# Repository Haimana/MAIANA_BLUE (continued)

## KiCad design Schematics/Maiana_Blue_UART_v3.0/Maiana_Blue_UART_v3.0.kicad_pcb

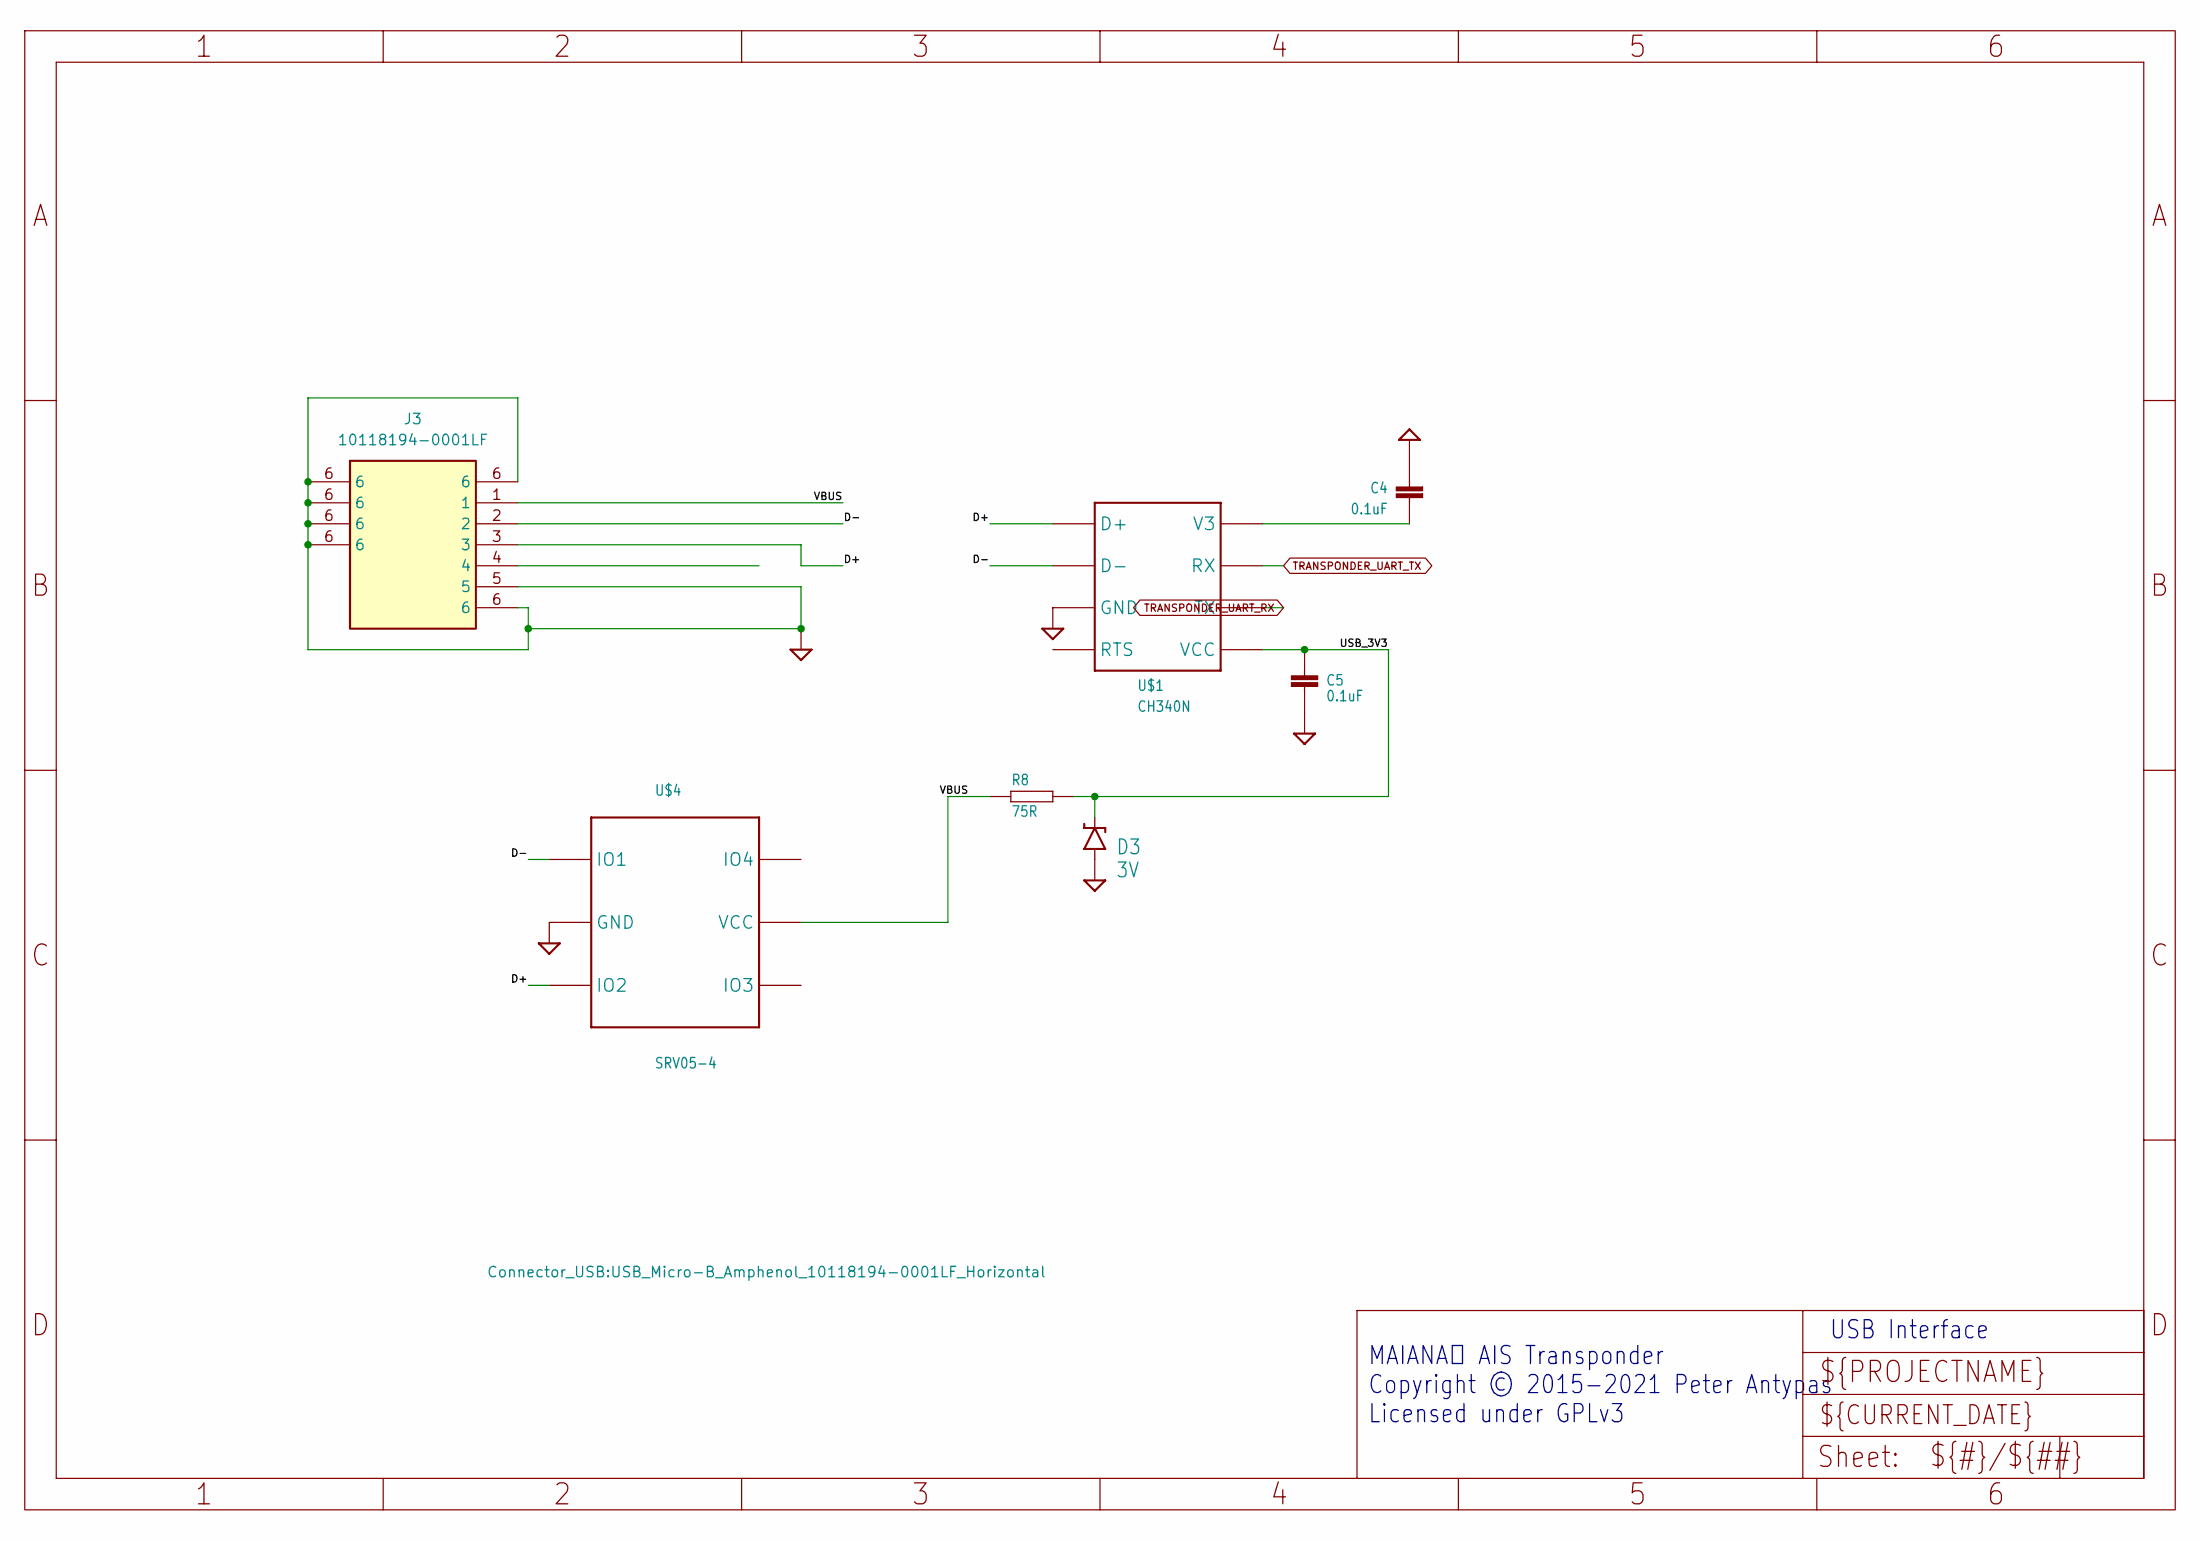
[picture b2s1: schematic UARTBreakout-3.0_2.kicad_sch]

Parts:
C4, C5: 0.1uF; 0603
D3: 3V; SOD-323
J3: 10118194-0001LF; USB_Micro-B_Amphenol_10118194-0001LF_Horizontal; Manufacturer_Part_Number 10118194-0001LF
R8: 75R; 0603
U$1: CH340N; SOIC-8; PARTNO CH340N
U$4: SRV05-4; SOT23-6

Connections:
/UARTBreakout-3.0_2/D+: J3.3, U$1.1 (D+), U$4.3 (IO2)
/UARTBreakout-3.0_2/D-: J3.2, U$1.2 (D-), U$4.1 (IO1)
/UARTBreakout-3.0_2/USB_3V3: C5.P$1 (1), D3.C, R8.P$2, U$1.5 (VCC)
/UARTBreakout-3.0_2/VBUS: J3.1, R8.P$1, U$4.5 (VCC)
GND: C4.P$2 (2), C5.P$2 (2), D3.A, J3.5, J3.6, U$1.3 (GND), U$4.2 (GND); also elsewhere on the board
unnamed: C4.P$1 (1), U$1.8 (V3)
TRANSPONDER_UART_RX: U$1.6 (TX); also elsewhere on the board
TRANSPONDER_UART_TX: U$1.7 (RX); also elsewhere on the board

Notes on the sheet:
USB Interface
MAIANA™ AIS Transponder Copyright © 2015-2021 Peter Antypas Licensed under GPLv3

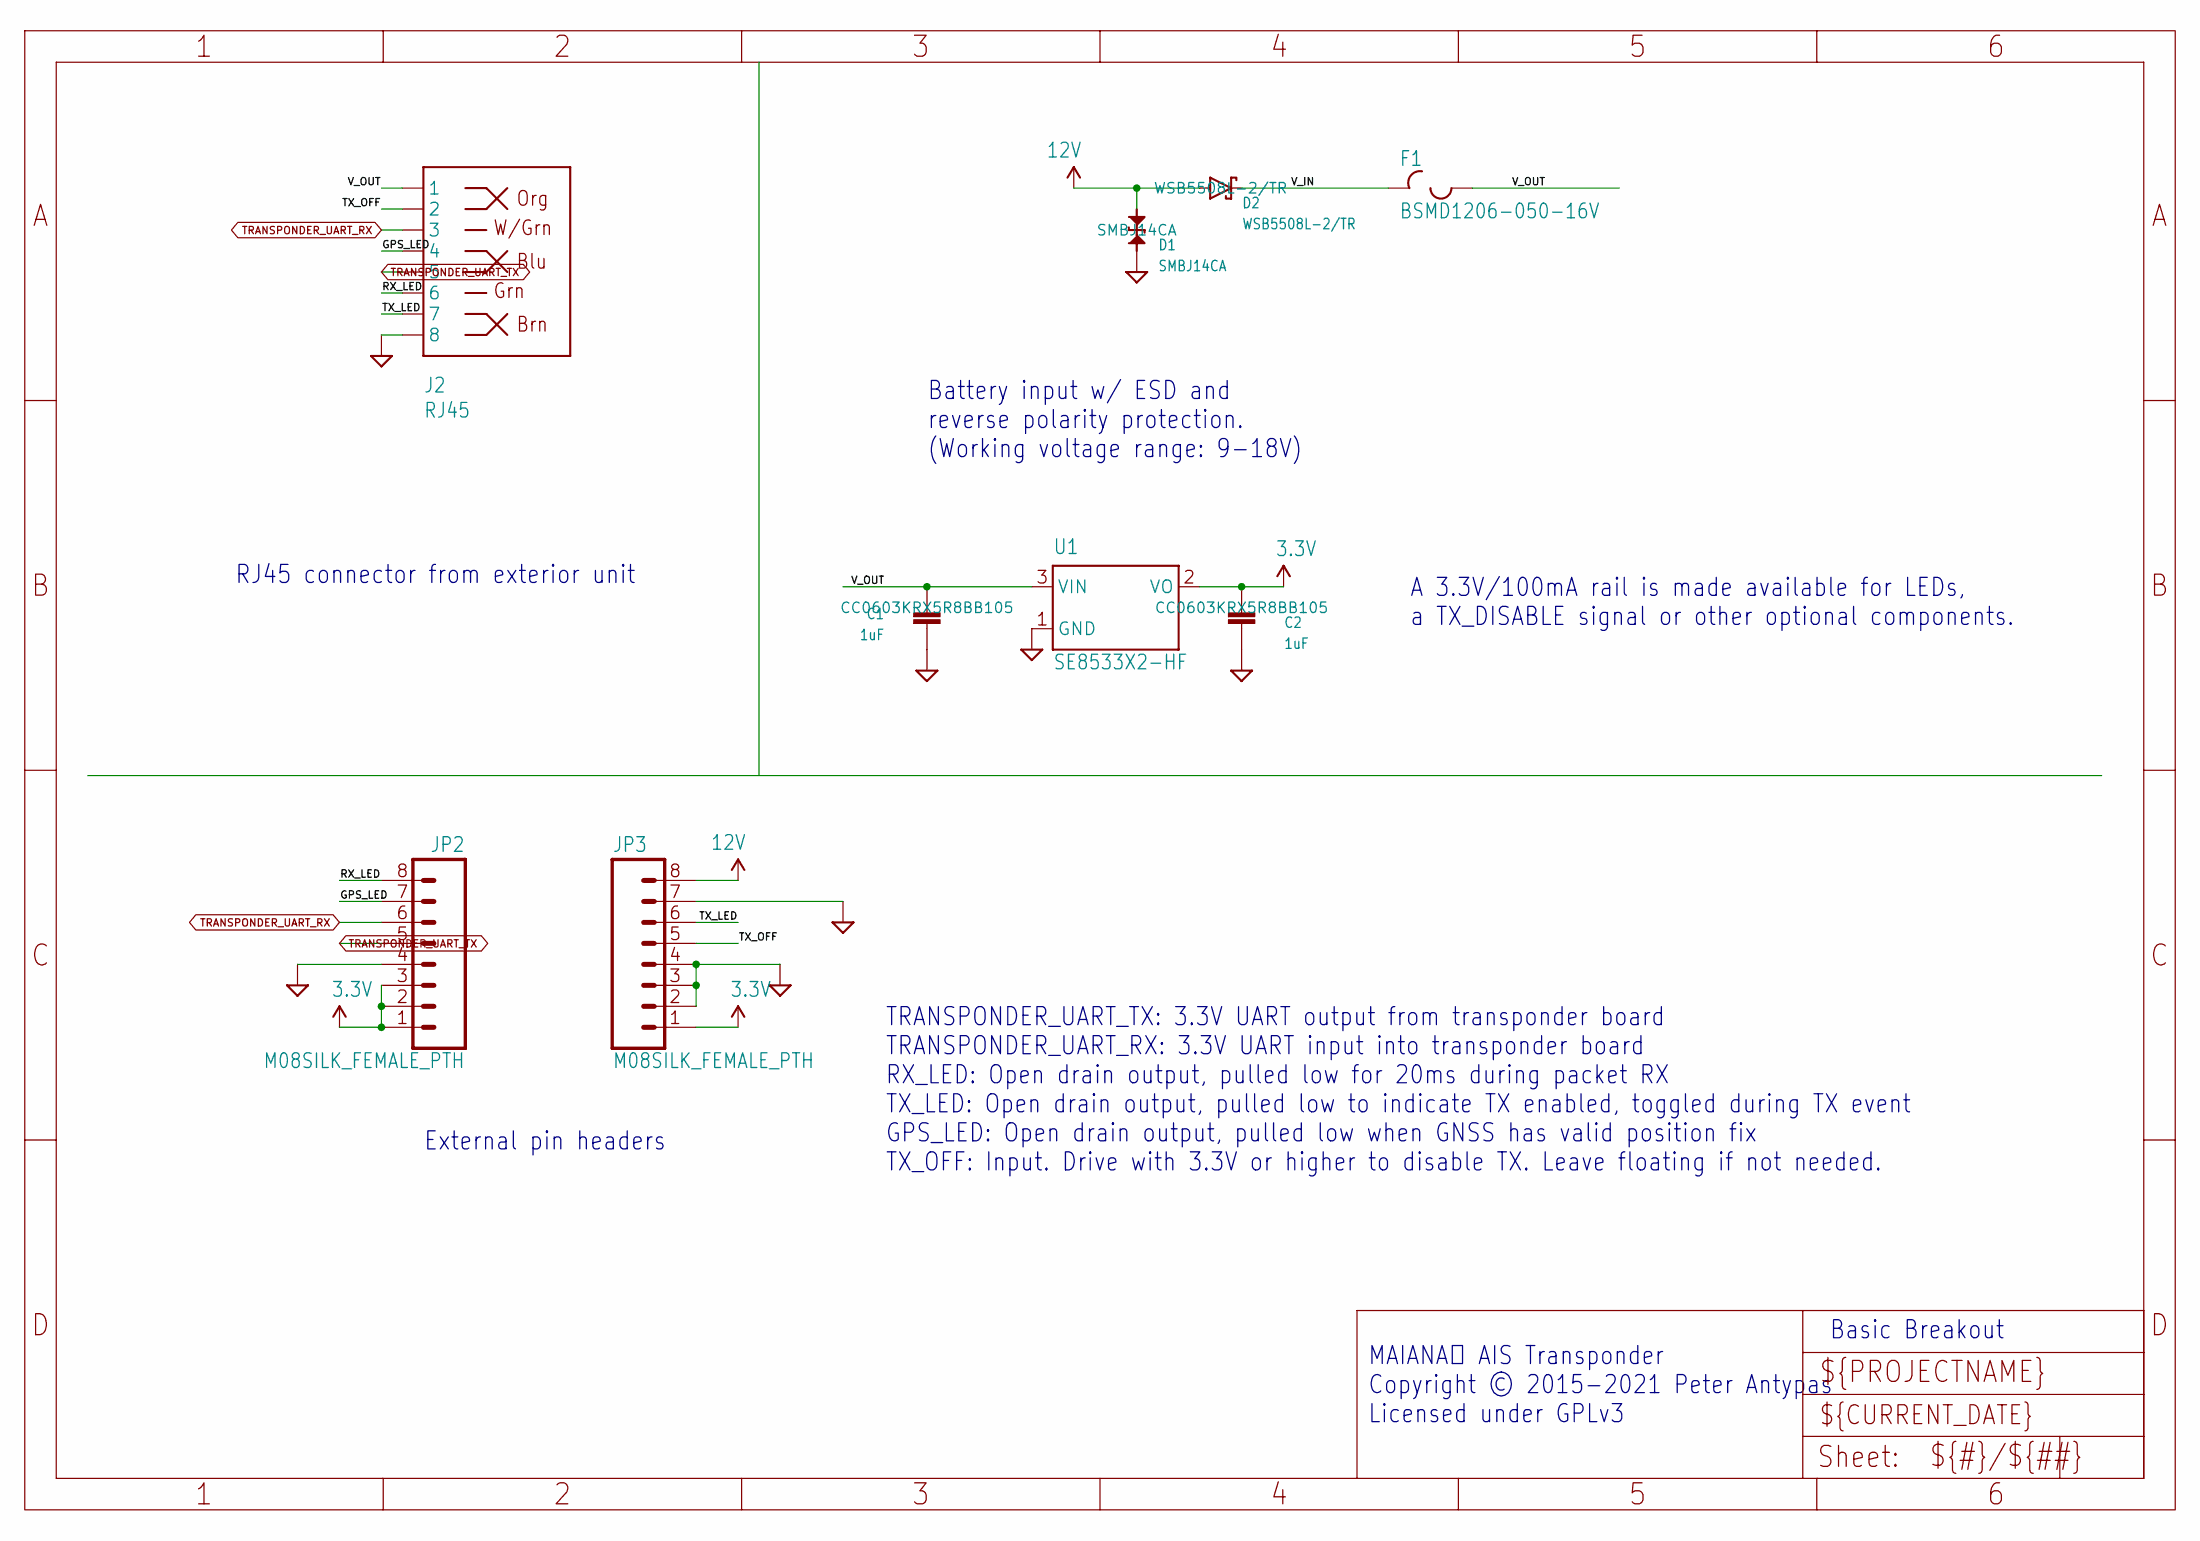
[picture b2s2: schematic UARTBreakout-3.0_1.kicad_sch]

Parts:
C1, C2: 1uF; 0603; PARTNO CC0603KRX5R8BB105
D1: SMBJ14CA; SMB-BIDIR; PARTNO SMBJ14CA
D2: WSB5508L-2/TR; SOD123; PARTNO WSB5508L-2/TR
F1: BSMD1206-050-16V; R1206; PARTNO BSMD1206-050-16V
J2: RJ45; RJ45-8; PARTNO 95501-2821
JP2, JP3: M08SILK_FEMALE_PTH; 1X08
U1: SE8533X2-HF; SOT23; PARTNO SE8533X2-HF

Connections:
3.3V: C2.P$1 (1), JP2.1, JP2.2, JP2.3, JP3.1, U1.2 (VO)
12V: D1.A, D2.A, JP3.8
/UARTBreakout-3.0_1/GPS_LED: J2.4, JP2.7
/UARTBreakout-3.0_1/RX_LED: J2.6, JP2.8
/UARTBreakout-3.0_1/TX_LED: J2.7, JP3.6
/UARTBreakout-3.0_1/TX_OFF: J2.2, JP3.5
/UARTBreakout-3.0_1/V_IN: D2.C, F1.1
/UARTBreakout-3.0_1/V_OUT: C1.P$1 (1), F1.2, J2.1, U1.3 (VIN)
GND: C1.P$2 (2), C2.P$2 (2), D1.C, J2.8, JP2.4, JP3.2, JP3.3, JP3.4, JP3.7, U1.1 (GND); also elsewhere on the board
TRANSPONDER_UART_RX: J2.3, JP2.6; also elsewhere on the board
TRANSPONDER_UART_TX: J2.5, JP2.5; also elsewhere on the board

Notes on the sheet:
TRANSPONDER_UART_TX: 3.3V UART output from transponder board TRANSPONDER_UART_RX: 3.3V UART input into transponder board RX_LED: Open drain output, pulled low for 20ms during packet RX TX_LED: Open drain output, pulled low to indicate TX enabled, toggled during TX event GPS_LED: Open drain output, 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
RJ45 connector from exterior unit
Basic Breakout
Battery input w/ ESD and reverse polarity protection. (Working voltage range: 9-18V)
A 3.3V/100mA rail is made available for LEDs, a TX_DISABLE signal or other optional components.
External pin headers
MAIANA™ AIS Transponder Copyright © 2015-2021 Peter Antypas Licensed under GPLv3

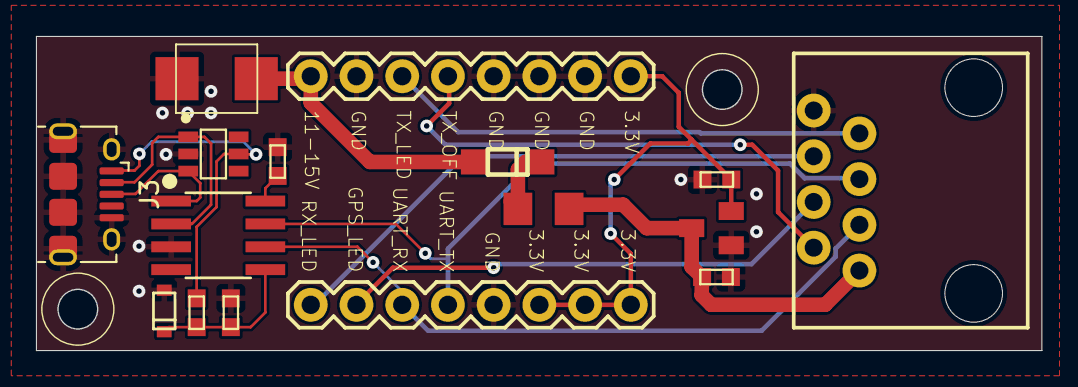
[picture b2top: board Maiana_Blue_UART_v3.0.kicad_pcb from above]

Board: 2 copper layers, 55.9 x 17.5 mm, 16 parts (0 on the bottom side), 16 nets.

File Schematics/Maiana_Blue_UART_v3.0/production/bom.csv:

Designator,Footprint,Quantity,Value,LCSC Part #
"C1, C2",0603,2,1uF,
"C4, C5",0603,2,0.1uF,
D1,SMB-BIDIR,1,SMBJ14CA,
D2,SOD123,1,WSB5508L-2/TR,
D3,SOD-323,1,3V,
F1,R1206,1,BSMD1206-050-16V,
J3,USB_Micro-B_Amphenol_10118194-0001LF_Horizontal,1,10118194-0001LF,
R8,0603,1,75R,
U$1,SOIC-8,1,CH340N,
U1,SOT23,1,SE8533X2-HF,

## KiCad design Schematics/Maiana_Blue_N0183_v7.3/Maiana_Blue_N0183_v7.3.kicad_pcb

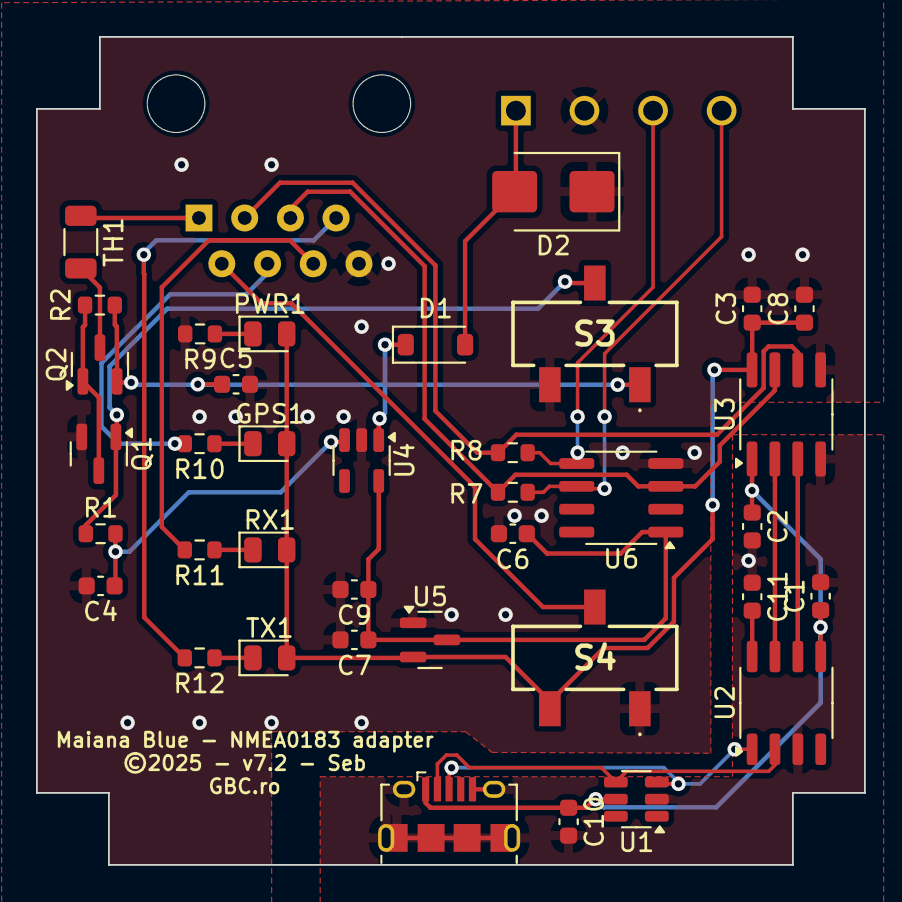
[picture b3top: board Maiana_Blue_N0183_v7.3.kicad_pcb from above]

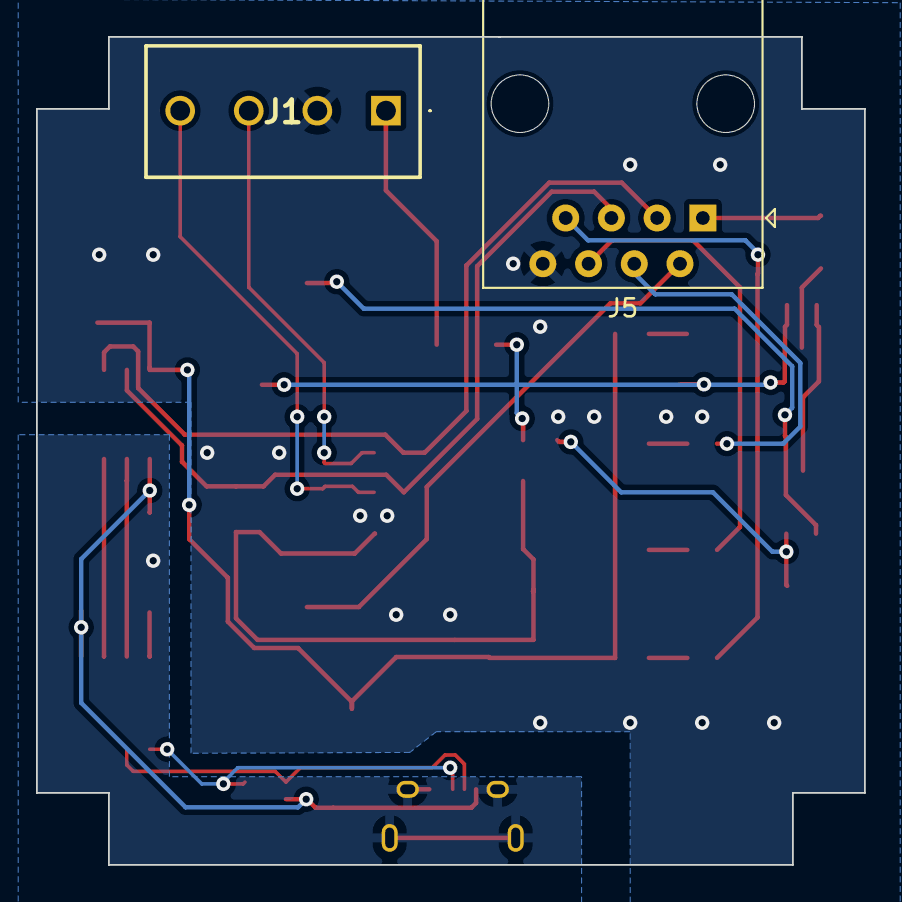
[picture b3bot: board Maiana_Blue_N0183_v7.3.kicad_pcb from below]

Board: 2 copper layers, 46.0 x 46.0 mm, 39 parts (2 on the bottom side), 29 nets.

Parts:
C1, C2, C3, C9, C10, C11: 0.1uF; C_0603_1608Metric
C4, C5, C6, C7, C8: 1uF; C_0603_1608Metric
D1: WSB5508L-2/TR; D_SOD-123
D2: SMBJ16CA; D_SMB
GPS1: KT-0805G; LED_0805_2012Metric
J1: 1727036
J3: USB_B_Micro; USB_Micro-B_Amphenol_10118194_Horizontal
J5: 54602-908LF; RJ45_Amphenol_54602-x08_Horizontal
PWR1: KT-0805G; LED_0805_2012Metric
Q1: BSS138; SOT-23
Q2: AO3401A; SOT-23
R1, R2: 10k; R_0603_1608Metric
R7, R8: 0R; R_0603_1608Metric
R9, R10, R11, R12: 2k2; R_0603_1608Metric
RX1: KT-0805G; LED_0805_2012Metric
S3, S4: MS-12D17-G2; MS12D17G2
TH1: Thermistor_PTC; R_1206_3216Metric
TX1: KT-0805G; LED_0805_2012Metric
U1: SRV05-4; SOT-23-6
U2: CH340N; SO-8_3.9x4.9mm_P1.27mm
U3: ADuM121N; SOIC-8_3.9x4.9mm_P1.27mm
U4: TJ5205SF5-5.0; SOT-23-5
U5: SE8533X2-HF; SOT-23
U6: DS8921M; SOIC-8_3.9x4.9mm_P1.27mm

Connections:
+3.3V: C3.1, C8.1, GPS1.2 (A), PWR1.2 (A), RX1.2 (A), S4.2, TX1.2 (A), U3.8 (VDD2), U5.2 (VO)
+5V: C6.1, C7.1, C9.1, U4.5 (VOUT), U5.3 (VI), U6.1 (VCC)
+12V: D1.2 (A), D2.2, J1.1
/TX_DISABLE: J5.2, S4.3
/VBUS: C1.1, C2.1, C10.1, J3.1 (VBUS), U1.5 (VP), U2.5 (VCC), U3.1 (VDD1)
/V_IN: C5.1, D1.1 (K), Q2.2 (S), R2.2, S3.1, U4.1 (VIN)
AIS_RX_EVENT: J5.6, R11.2
AIS_TX_EVENT: J5.7, R12.2
D+: J3.3 (D+), U1.3 (IO2), U2.1 (D+)
D-: J3.2 (D-), U1.4 (IO3), U2.2 (D-)
GND: C3.2, C4.2, C5.2, C6.2, C7.2, C8.2, C9.2, D2.1, J1.2, J5.8, Q1.2 (S), R9.2, S3.2, S4.1, U3.5 (GND2), U4.2 (GND), U5.1 (GND), U6.4 (GND)
GND2: C1.2, C2.2, C10.2, C11.1, J3.5 (GND), J3.6 (Shield), U1.2 (VN), U2.3 (GND), U3.4 (GND1)
GPS_STATUS: J5.4, R10.2
NMEA+: J1.4, R7.1, U6.6 (DO)
NMEA-: J1.3, R8.1, U6.5 (~DO)
unnamed: GPS1.1 (K), R10.1
unnamed: PWR1.1 (K), R9.1
unnamed: Q1.3 (D), Q2.1 (G), R2.1
unnamed: Q2.3 (D), TH1.2
unnamed: R11.1, RX1.1 (K)
unnamed: R12.1, TX1.1 (K)
unnamed: C11.2, U2.8 (V3)
unnamed: C4.1, R1.2, U4.3 (EN)
PWR_CTRL: Q1.1 (G), R1.1, S3.3
TRANSPONDER_RX_ISO: U2.6 (TX), U3.3 (VIB)
TRANSPONDER_TX_ISO: U2.7 (RX), U3.2 (VOA)
TRANSPONDER_UART_RX: J5.3, R8.2, U3.6 (VOB)
TRANSPONDER_UART_TX: J5.5, R7.2, U3.7 (VIA), U6.3 (DI)
V_OUT: J5.1, TH1.1

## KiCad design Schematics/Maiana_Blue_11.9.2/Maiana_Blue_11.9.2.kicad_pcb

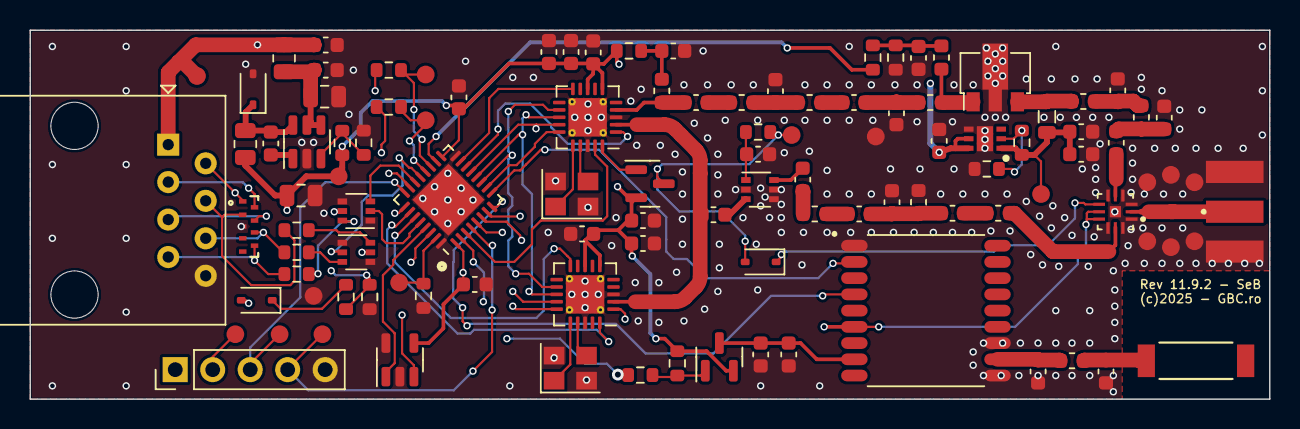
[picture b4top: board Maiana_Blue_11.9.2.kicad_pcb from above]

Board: 4 copper layers, 84.0 x 25.0 mm, 110 parts (0 on the bottom side), 80 nets.

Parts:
AE1: 1575AT43A0040E; ANT_1575AT_JOT
C1, C2, C8, C9: 0.1uf; C_0603_1608Metric
C3: 10uF; C_0805_2012Metric
C4, C7, C13, C14, C15: 2.2uF; C_0603_1608Metric
C5, C12, C16, C17, C21, C29: 22nF; C_0603_1608Metric
C6: 22uF; C_0805_2012Metric
C10: 2.2pF; C_0603_1608Metric
C11: 4pF; C_0603_1608Metric
C18, C19, C24: 91pF; C_0603_1608Metric
C20, C22, C30, C35: 2.2nF; C_0603_1608Metric
C23, C25: 3.3pF; C_0603_1608Metric
C26: 20pF; C_0603_1608Metric
C27, C32: 470pF; C_0603_1608Metric
C28: 16pF; C_0603_1608Metric
C31, C33: 110pF; C_0603_1608Metric
C34: 36pF; C_0603_1608Metric
CR1: D3V3X8U9LP3810-7; U-DFN3810-9TYPE_B_DIO
D1, D2, D3: BAT54WS; D_SOD-323
IC1: LDFPVR; SON65P200X200X100-7N-D
J1: RJ45; RJ45_Amphenol_54602-x08_Horizontal
J2: Conn_01x05; PinHeader_1x05_P2.54mm_Vertical
J3: CON-SMA-EDGE-S; RFSOLUTIONS_CON-SMA-EDGE-S
L1, L2: 4.7uH; R_0805_2012Metric
L3: 5.6nH; L_0603_1608Metric
L4, L6: 270nH; L_0603_1608Metric
L5: 10nH; L_0603_1608Metric
L7, L11: 470nH; L_0603_1608Metric
L8: 47nH; L_0603_1608Metric
L9: 68nH; L_0603_1608Metric
L10: 20nH; L_0603_1608Metric
L12: 2.2uH; L_0805_2012Metric
L13: 13nH; L_0603_1608Metric
L14: 39nH; L_0603_1608Metric
Q1: AO3409; SOT-23
Q2: AO3401A; SOT-23
Q3: AFT05MS004NT1; SOT-89-3
R1, R2, R3: 100R; R_0603_1608Metric
R4, R11, R12, R13, R18: 10k; R_0603_1608Metric
R5, R6, R7: 1k; R_0603_1608Metric
R8: 51k; R_0603_1608Metric
R9: 16k; R_0603_1608Metric
R10: 47k; R_0603_1608Metric
R14: 0; R_0603_1608Metric
R15: 220R; R_0603_1608Metric
R16: 22R; R_0603_1608Metric
R17: 3k3; R_0603_1608Metric
TP1, TP2, TP3, TP4, TP5, TP6, TP7, TP8, TP9, TP10, TP11, TP12, TP14, TP15, TP16, TP17, TP18, TP19: TP_1.2MM
TP13: TP_1.0MM
U1, U2: SI1926DL-T1-E3; SOT-363_SC-70-6
U3: AP3211K; SOT-23-6
U4: 24LC01BT/OT; SOT-23-5
U5: STM32L432KBUx; QFN-32-1EP_5x5mm_P0.5mm_EP3.45x3.45mm
U6: L76L-M33; XCVR_L76L-M33
U7, U8: Si4460; QFN-20-1EP_4x4mm_P0.5mm_EP2.6x2.6mm_ThermalVias
U9: BGA2800,115; SOT-363_SC-70-6
U10: SKY13330-397LF; QFN50P200X200X65-13N
Y1, Y2: ECS-300-10-33B-CKM-TR; Crystal_SMD_3225-4Pin_3.2x2.5mm

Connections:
+3.3V: C6.1, C8.2, C9.2, C14.2, C15.2, C16.2, C17.2, C18.2, C19.2, J2.1, L2.2, Q1.2 (S), Q2.2 (S), R8.1, R13.1, R16.1, TP6.1, U4.4 (V_{CC}), U5.1 (VDD), U5.5 (VDDA), U5.17 (VDD), U6.6 (V_BCKP), U7.6 (VDD), U7.8 (VDD), U8.6 (VDD), U8.8 (VDD), U10.8 (EN), U10.9 (VCC)
/Connections/GPS_STATUS: U1.2 (G1), U5.21 (PA11)
/Connections/HOST_GPS_STATUS: CR1.2, J1.4, R1.1
/Connections/HOST_RX_STATUS: CR1.7, J1.6, R2.1
/Connections/HOST_TX_OFF: CR1.1, D1.2 (A), J1.2
/Connections/HOST_TX_STATUS: CR1.6, J1.7, R3.1
/Connections/HOST_UART_RX: CR1.8, J1.5, R6.1
/Connections/HOST_UART_TX: CR1.9, J1.3, R7.1
/Connections/MCU_TX_OFF: U2.3 (D2), U5.22 (PA12)
/Connections/MCU_UART_RX: R7.2, TP2.1, U5.20 (PA10)
/Connections/MCU_UART_TX: R6.2, TP1.1, U5.19 (PA9)
/Connections/RX_STATUS: U1.5 (G2), U5.7 (PA1)
/Connections/TX_STATUS: U2.2 (G1), U5.28 (PB5)
/Connections/V_IN: C1.2, C4.2, IC1.5 (EN), IC1.6 (VIN), J1.1, L1.1, TP3.1
/GNSS/GPS_1PPS: U5.8 (PA2), U6.4 (1PPS)
/GNSS/GPS_EN: R14.2, U5.2 (PC14)
/GNSS/GPS_OUT: U5.9 (PA3), U6.2 (TXD1)
/MCU/RX_CLK: U5.26 (PB3), U8.20 (GPIO3)
/MCU/RX_CS: U5.6 (PA0), U8.15 (~SEL)
/MCU/RX_DATA: U5.27 (PB4), U8.10 (GPIO1)
/MCU/RX_SDN: U5.25 (PA15), U8.1 (SDN)
/MCU/SPI_MISO: U5.12 (PA6), U7.13 (SDO), U8.13 (SDO)
/MCU/SPI_MOSI: U5.13 (PA7), U7.14 (SDI), U8.14 (SDI)
/MCU/SPI_SCK: U5.11 (PA5), U7.12 (SCLK), U8.12 (SCLK)
/MCU/TRX_CKL: U5.3 (PC15), U7.19 (GPIO2)
/MCU/TRX_CS: U5.10 (PA4), U7.15 (~SEL)
/MCU/TRX_DATA: U5.15 (PB1), U7.10 (GPIO1)
/MCU/TRX_SDN: U5.14 (PB0), U7.1 (SDN)
/MCU/V_PA_BIAS: R17.1, U5.18 (PA8)
/Power/V_PA: C7.2, C32.2, IC1.1 (VOUT), L12.1, R10.1, TP7.1
/Receiver/RF_IN: L6.2, U10.11 (RF2)
/Receiver/TRX_OUT: C26.1, L7.1, U7.4 (TX)
/Receiver/V_LNA: D3.2 (A), Q2.3 (D), R15.1, TP12.1
GND: C1.1, C2.1, C3.2, C4.1, C6.2, C7.1, C8.1, C9.1, C10.1, C11.1, C12.1, C13.1, C14.1, C15.1, C16.1, C17.1, C18.1, C19.1, C21.2, C24.1, C27.1, C28.1, C29.1, C31.1, C32.1, C33.1, C34.1, CR1.3, D2.2 (A), IC1.4 (GND_1), IC1.7 (GND_2), J1.8, J2.5, J3.G1, J3.G2, J3.G3, J3.G4, L5.1, Q3.2 (S), R4.2, R9.2, R11.2, R12.2, R18.2, TP4.1, TP5.1, TP14.1, TP15.1, TP16.1, TP17.1, TP18.1, TP19.1, U1.1 (S1), U1.4 (S2), U2.1 (S1), U2.4 (S2), U3.2 (GND), U4.2 (V_{SS}), U4.5 (WP), U5.16 (VSS), U5.32 (VSS), U5.33 (VSS), U6.1 (GND), U6.10 (GND), U6.12 (GND), U7.3 (RXn), U7.18 (GND), U7.21 (GND), U8.3 (RXn), U8.18 (GND), U8.21 (GND), U9.2 (G), U9.4 (G), U9.5 (G), U10.1 (GND), U10.3 (GND), U10.4 (GND), U10.6 (GND), U10.10 (GND), U10.12 (GND), U10.13 (GND), Y1.2, Y1.4, Y2.2, Y2.4
NRST: J2.4, TP11.1, U5.4 (NRST)
unnamed: AE1.1, C10.2, L3.1
unnamed: C20.2, U9.3
unnamed: C22.1, U9.6
unnamed: C22.2, L4.1
unnamed: C23.1, C24.2, C25.1, L5.2
unnamed: C23.2, L4.2
unnamed: C25.2, L6.1
unnamed: C26.2, L8.1
unnamed: C27.2, L7.2, R16.2
unnamed: C28.2, L8.2, L9.1
unnamed: C29.2, L11.2, R17.2, R18.1
unnamed: C30.1, L9.2
unnamed: C30.2, C31.2, L10.1
unnamed: C33.2, L13.2, L14.1
unnamed: C34.2, C35.1, L14.2
unnamed: D1.1 (K), R5.2
unnamed: C5.2, D2.1 (K), L2.1, U3.6 (SW)
unnamed: D3.1 (K), U10.7 (CTRL)
unnamed: IC1.2 (ADJ/NC), R10.2, R11.1
unnamed: C12.2, C13.2, Q1.3 (D), U6.8 (VCC)
unnamed: Q1.1 (G), R13.2, R14.1
unnamed: Q2.1 (G), U7.20 (GPIO3)
unnamed: L12.2, L13.1, Q3.3 (D)
unnamed: L10.2, L11.1, Q3.1 (G)
unnamed: R12.1, TP8.1, U5.31 (PH3)
unnamed: J3.1, TP13.1, U10.2 (RF1)
unnamed: R1.2, U1.6 (D1)
unnamed: R2.2, U1.3 (D2)
unnamed: R3.2, U2.6 (D1)
unnamed: R4.1, R5.1, U2.5 (G2)
unnamed: C5.1, U3.1 (BS)
unnamed: C2.2, C3.1, L1.2, U3.4 (EN), U3.5 (IN)
unnamed: R8.2, R9.1, U3.3 (FB)
unnamed: U4.1 (SCL), U5.29 (PB6)
unnamed: U4.3 (SDA), U5.30 (PB7)
unnamed: C11.2, L3.2, U6.11 (RF_IN)
unnamed: C20.1, U7.2 (RXp), U8.2 (RXp)
unnamed: U7.17 (XIN), Y2.3
unnamed: U7.16 (XOUT), Y2.1
unnamed: U8.17 (XIN), Y1.3
unnamed: U8.16 (XOUT), Y1.1
unnamed: C21.1, R15.2, U9.1 (Vcc)
PA_OUT: C35.2, U10.5 (RF3)
SWCLK: J2.3, TP10.1, U5.24 (PA14)
SWDIO: J2.2, TP9.1, U5.23 (PA13)

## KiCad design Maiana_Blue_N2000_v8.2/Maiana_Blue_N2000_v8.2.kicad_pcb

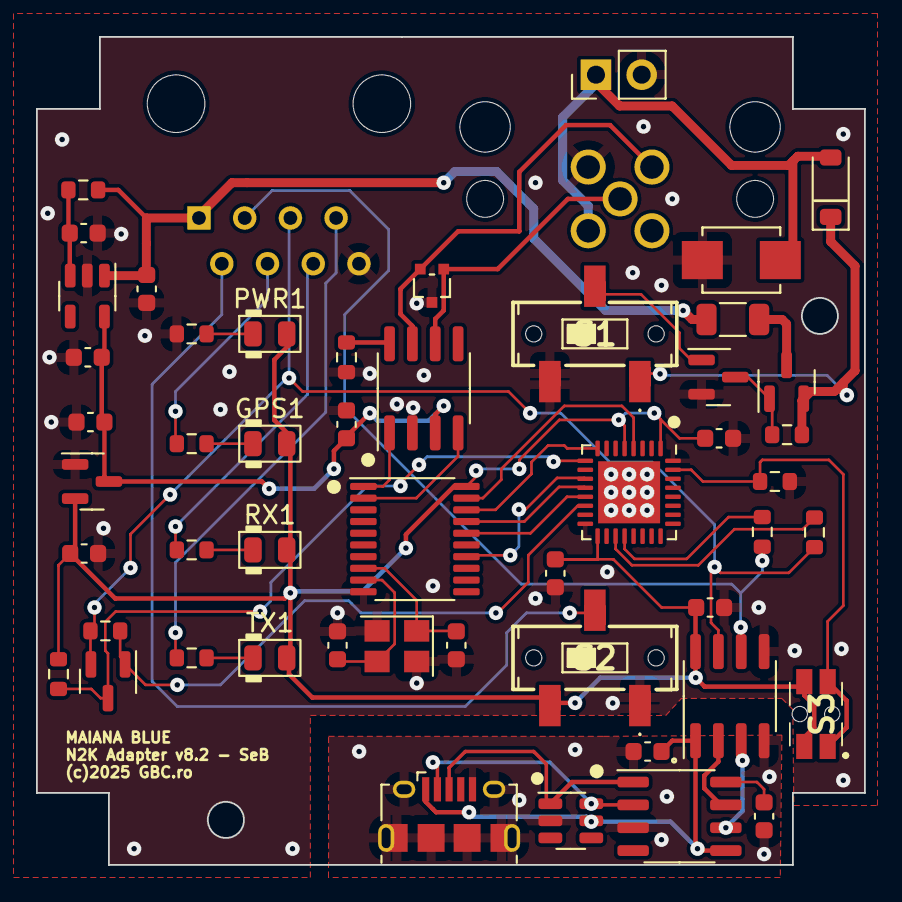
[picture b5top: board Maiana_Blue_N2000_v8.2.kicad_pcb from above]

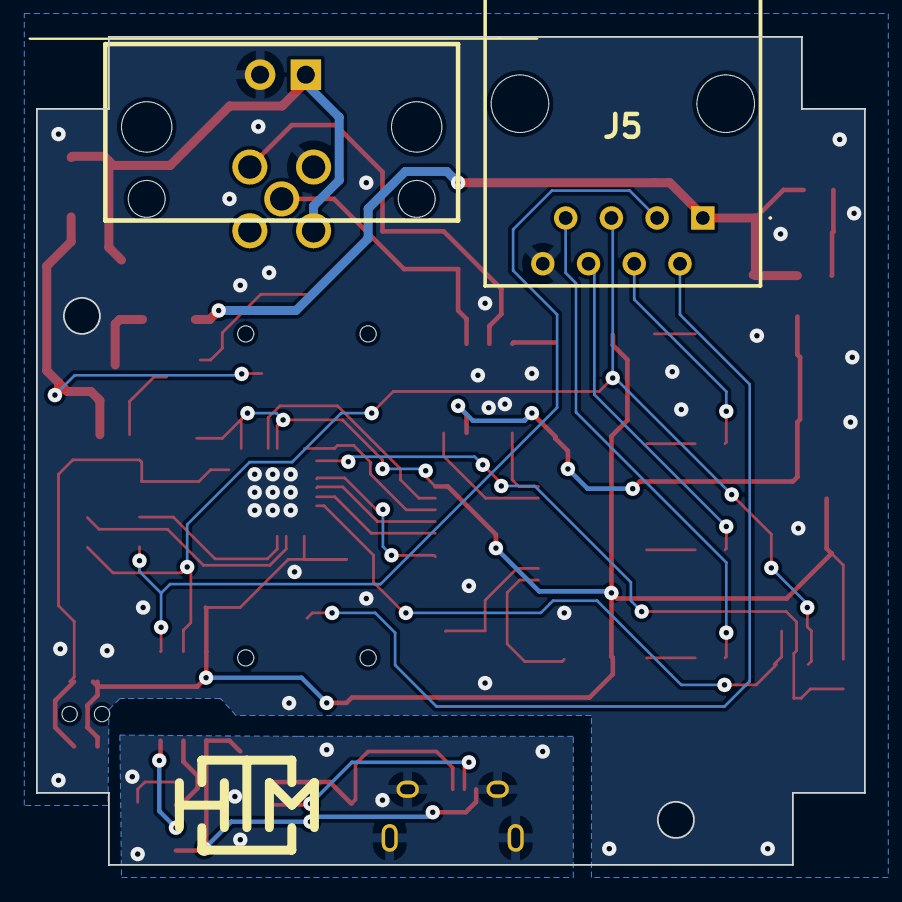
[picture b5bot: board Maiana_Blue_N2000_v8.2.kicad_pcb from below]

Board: 2 copper layers, 46.0 x 46.0 mm, 54 parts (2 on the bottom side), 44 nets.

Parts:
C1, C2, C3, C11, C12, C13: 0.1uF; C_0603_1608Metric
C4, C5: 20pF; C_0603_1608Metric
C6, C7, C8, C9, C10: 1uF; C_0603_1608Metric
D5: PESD1CAN-U; SOT323
D6: SMBJ16CA; DIOM4336X265N
D8: D_Schottky; D_SOD-123
GPS1: KT-0805G; LED_0805_2012Metric
J1: 12-3701-05; MICRO_C_5PIN
J3: USB_B_Micro; USB_Micro-B_Amphenol_10118194_Horizontal
J4: Conn_01x02; PinHeader_1x02_P2.54mm_Vertical
J5: 54602-908LF; 54602908LF
PWR1: KT-0805G; LED_0805_2012Metric
Q1, Q3: BSS138; SOT-23
Q2: AO3401A; SOT-23
R1, R2, R3, R4: 2k2; R_0603_1608Metric
R5, R6, R7, R8, R9, R10: 10k; R_0603_1608Metric
R11, R12: 0R; R_0603_1608Metric
RX1: KT-0805G; LED_0805_2012Metric
S1, S2: MS-12D17-G2; MS12D17G2
S3: SKSCLDE010
SW1, SW2: CL-SB-12B-01T
TH1: BSMD1206-050-16V; R_1206_3216Metric
TX1: KT-0805G; LED_0805_2012Metric
U1: STM32L432KBUx; QFN-32-1EP_5x5mm_P0.5mm_EP3.45x3.45mm
U2: MCP2515-xST; TSSOP-20_4.4x6.5mm_P0.65mm
U3: MCP2551-I-SN; SOIC-8_3.9x4.9mm_P1.27mm
U4: SRV05-4; SOT-23-6
U5: CH340N; SO-8_3.9x4.9mm_P1.27mm
U6: ISO7721FDR; SOIC-8_3.9x4.9mm_P1.27mm
U7: TJ5205SF5-5.0; SOT-23-5
U8: SE8533X2-HF; SOT-23
Y1: X322516MOB4SI; Crystal_SMD_3225-4Pin_3.2x2.5mm

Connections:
+3.3V: C2.1, C10.1, C12.1, C13.1, GPS1.2 (A), PWR1.2 (A), R10.1, RX1.2 (A), S2.2, S3.3 (NO), S3.4 (NO), SW2.1, TX1.2 (A), U1.1 (VDD), U1.5 (VDDA), U1.17 (VDD), U2.20 (VDD), U6.8 (VDD2), U8.2 (VO)
+5V: C8.1, C9.1, C11.1, U3.3 (VDD), U7.5 (OUT), U8.3 (VI)
+12V: D6.2, D8.2 (A), J1.2, J4.1
/CAN/CAN_H: D5.2, J1.4, U3.7 (CANH)
/CAN/CAN_L: D5.1, J1.5, U3.6 (CANL)
/CAN/NRST: U1.4 (NRST), U2.19 (~RESET)
/CAN/SPI_CS: U1.8 (PA2), U2.18 (~CS)
/CAN/SPI_MISO: U1.12 (PA6), U2.17 (SO)
/CAN/SPI_MOSI: U1.13 (PA7), U2.16 (SI)
/CAN/SPI_SCK: U1.11 (PA5), U2.14 (SCK)
/Connections/AIS_RX_EVENT: J5.6, R3.2
/Connections/AIS_TX_EVENT: J5.7, R4.2
/Connections/GPS_STATUS: J5.4, R2.2
/Connections/MCU_UART_RX: R12.2, U1.20 (PA10)
/Connections/MCU_UART_TX: R11.2, U1.19 (PA9)
/Connections/TRANSPONDER_UART_TX: J5.5, Q3.2 (S), R9.2, R11.1, U6.7 (VIA)
/Connections/TX_DISABLE: J5.2, S2.3, SW2.C
/Connections/V_OUT: C7.1, J5.1, R6.1, TH1.1, U7.1 (IN)
/MCU/BOOT0: R8.1, S3.1 (NO), S3.2 (NO), U1.31 (PH3)
/Power/PWR_CTRL: Q1.1 (G), S1.3, SW1.C
/Power/V_IN: D8.1 (K), Q2.2 (S), R5.1, S1.1, SW1.3
CH340_RX: U5.7 (RX), U6.2 (VOA)
CH340_TX: U5.6 (TX), U6.3 (VIB)
D+: J3.3 (D+), U4.1 (IO1), U5.1 (D+)
D-: J3.2 (D-), U4.6 (IO4), U5.2 (D-)
GND: C2.2, C4.2, C5.2, C6.2, C7.2, C8.2, C9.2, C10.2, C11.2, C12.2, C13.2, D5.3, D6.1, J1.3, J4.2, J5.8, Q1.2 (S), R1.2, R7.2, R8.2, S1.2, S2.1, SW1.1, SW2.3, U1.16 (VSS), U1.32 (VSS), U1.33 (VSS), U2.10 (VSS), U3.2 (VSS), U6.5 (GND2), U7.2 (GND), U8.1 (GND), Y1.2, Y1.4
GND2: C1.2, C3.2, J3.5 (GND), J3.6 (Shield), U4.2 (VN), U5.3 (GND), U6.4 (GND1)
NMEA_RX: Q3.3 (D), R10.2, U1.9 (PA3)
NMEA_RX_EN: Q3.1 (G), R9.1, U1.14 (PB0)
unnamed: GPS1.1 (K), R2.1
unnamed: PWR1.1 (K), R1.1
unnamed: Q1.3 (D), Q2.1 (G), R5.2
unnamed: Q2.3 (D), TH1.2
unnamed: R3.1, RX1.1 (K)
unnamed: R4.1, TX1.1 (K)
unnamed: U2.2 (RXCAN), U3.4 (RXD)
unnamed: U2.1 (TXCAN), U3.1 (TXD)
unnamed: R7.1, U3.8 (Rs)
unnamed: C1.1, U5.8 (V3)
unnamed: C6.1, R6.2, U7.3 (EN)
TRANSPONDER_UART_RX: J5.3, R12.1, U6.6 (VOB)
VBUS: C3.1, J3.1 (VBUS), U4.5 (VP), U5.5 (VCC), U6.1 (VDD1)
XTL1: C5.1, U2.8 (OSC2), Y1.1
XTL2: C4.1, U2.9 (OSC1), Y1.3

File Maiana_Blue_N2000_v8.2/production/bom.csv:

Designator,Footprint,Quantity,Value,LCSC Part #
"C1, C11, C12, C13, C2, C3",0603,6,0.1uF,
"C10, C6, C7, C8, C9",0603,5,1uF,
"C4, C5",0603,2,20pF,
D5,SOT323,1,PESD1CAN-U,
D6,DIOM4336X265N,1,SMBJ16CA,
D8,D_SOD-123,1,D_Schottky,
"GPS1, PWR1, RX1, TX1",0805,4,KT-0805G,
J3,USB_Micro-B_Amphenol_10118194_Horizontal,1,USB_B_Micro,
"Q1, Q3",SOT-23,2,BSS138,
Q2,SOT-23,1,AO3401A,
"R1, R2, R3, R4",0603,4,2k2,
"R10, R5, R6, R7, R8, R9",0603,6,10k,
"R11, R12",0603,2,0R,
"S1, S2",MS12D17G2,2,MS-12D17-G2,
S3,SKSCLDE010,1,SKSCLDE010,
TH1,1206,1,BSMD1206-050-16V,
U1,QFN-32-1EP_5x5mm_P0.5mm_EP3.45x3.45mm,1,STM32L432KBUx,
U2,TSSOP-20_4.4x6.5mm_P0.65mm,1,MCP2515-xST,
U3,SOIC-8_3.9x4.9mm_P1.27mm,1,MCP2551-I-SN,
U4,SOT-23-6,1,SRV05-4,
U5,SO-8_3.9x4.9mm_P1.27mm,1,CH340N,
U6,SOIC-8_3.9x4.9mm_P1.27mm,1,ISO7721FDR,
U7,SOT-23-5,1,TJ5205SF5-5.0,
U8,SOT-23,1,SE8533X2-HF,
Y1,Crystal_SMD_3225-4Pin_3.2x2.5mm,1,X322516MOB4SI,

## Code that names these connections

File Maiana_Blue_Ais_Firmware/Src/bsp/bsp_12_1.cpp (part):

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
static const GPIO __gpios[] = {
    // Initialize all SPI chip-select and RF shutdown lines HIGH first (before
    // SPI1 AF pins) so no slave sees a glitch; PB6 has no external pull-up.
    {EEPROM_CS_PORT, {EEPROM_CS_PIN, GPIO_MODE_OUTPUT_PP, GPIO_PULLUP, GPIO_SPEED_HIGH, 0}, GPIO_PIN_SET},
    {CS1_PORT, {CS1_PIN, GPIO_MODE_OUTPUT_PP, GPIO_NOPULL, GPIO_SPEED_HIGH, 0}, GPIO_PIN_SET},
    {CS2_PORT, {CS2_PIN, GPIO_MODE_OUTPUT_PP, GPIO_NOPULL, GPIO_SPEED_HIGH, 0}, GPIO_PIN_SET},
    {SDN1_PORT, {SDN1_PIN, GPIO_MODE_OUTPUT_PP, GPIO_NOPULL, GPIO_SPEED_LOW, 0}, GPIO_PIN_SET},
    {SDN2_PORT, {SDN2_PIN, GPIO_MODE_OUTPUT_PP, GPIO_NOPULL, GPIO_SPEED_LOW, 0}, GPIO_PIN_SET},
    {GNSS_EN_PORT, {GNSS_EN_PIN, GPIO_MODE_OUTPUT_OD, GPIO_NOPULL, GPIO_SPEED_LOW, 0}, GPIO_PIN_SET},
    {TRX_IC_CLK_PORT, {TRX_IC_CLK_PIN, GPIO_MODE_IT_RISING, GPIO_NOPULL, GPIO_SPEED_LOW, 0}, GPIO_PIN_RESET},
    {TX_DISABLE_PORT, {TX_DISABLE_PIN, GPIO_MODE_INPUT, GPIO_PULLUP, GPIO_SPEED_LOW, 0}, GPIO_PIN_SET},
    {RX_EVT_PORT, {RX_EVT_PIN, GPIO_MODE_OUTPUT_PP, GPIO_NOPULL, GPIO_SPEED_LOW, 0}, GPIO_PIN_RESET},
    // GNSS starts powered off (GNSS_EN = SET); keep PA2/PA3 in analog Hi-Z
    // until bsp_gnss_on() so USART2_TX idle HIGH cannot back-power U4.
    {GNSS_NMEA_TX_PORT, {GNSS_NMEA_TX_PIN, GPIO_MODE_ANALOG, GPIO_NOPULL, GPIO_SPEED_LOW, 0}, GPIO_PIN_RESET},
    {GNSS_NMEA_RX_PORT, {GNSS_NMEA_RX_PIN, GPIO_MODE_ANALOG, GPIO_NOPULL, GPIO_SPEED_LOW, 0}, GPIO_PIN_RESET},
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  HAL_Delay(10);
  eeprom_init();

  // USART2 (bidirectional GNSS link: PA2 = TX, PA3 = RX)
  huart2.Instance                     = USART2;
  huart2.Init.BaudRate                = 115200;
  huart2.Init.WordLength              = UART_WORDLENGTH_8B;
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
  HAL_TIM_Base_Init(&htim2);

  // 1PPS signal on PB7 (EXTI7 -> EXTI9_5_IRQn)
  HAL_NVIC_SetPriority(EXTI9_5_IRQn, 6, 0);
  HAL_NVIC_EnableIRQ(EXTI9_5_IRQn);

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  HAL_NVIC_SetPriority(TIM2_IRQn, 1, 0);
  HAL_NVIC_EnableIRQ(TIM2_IRQn);

  // RF IC clock interrupts (PC15 -> EXTI15_10, PB3 -> EXTI3)
  HAL_NVIC_SetPriority(EXTI15_10_IRQn, 1, 0);
  HAL_NVIC_EnableIRQ(EXTI15_10_IRQn);

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}

/*
 * M95040-DR SPI EEPROM helpers (shared SPI1 bus with PB6 active-low CS).
 */

static uint8_t sEepromInitStatus = BSP_NVM_NOT_RESPONDING;
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
static inline void eeprom_cs_low()
{
  HAL_GPIO_WritePin(EEPROM_CS_PORT, EEPROM_CS_PIN, GPIO_PIN_RESET);
}

static inline void eeprom_cs_high()
{
  HAL_GPIO_WritePin(EEPROM_CS_PORT, EEPROM_CS_PIN, GPIO_PIN_SET);
}

static inline void eeprom_cs_deselect_delay()
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void bsp_gnss_on()
{
  HAL_GPIO_WritePin(GNSS_EN_PORT, GNSS_EN_PIN, GPIO_PIN_RESET);
  // Let Q2 bring U4 VCC up before driving PA2 (USART2_TX) high
  HAL_Delay(2);
  gnss_uart_pins_enable();

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
void bsp_gnss_off()
{
  // Put PA2/PA3 into analog Hi-Z before turning Q2 off to prevent back-powering U4
  gnss_uart_pins_disable();
  HAL_GPIO_WritePin(GNSS_EN_PORT, GNSS_EN_PIN, GPIO_PIN_SET);
}
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
bool bsp_is_tx_disabled()
{
  return HAL_GPIO_ReadPin(TX_DISABLE_PORT, TX_DISABLE_PIN) == GPIO_PIN_RESET;
}

void bsp_enter_dfu()
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
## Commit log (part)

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2025-07-29 Initial upload. Maiana Blue Transponder Schematic v11.9.2
2025-07-29 Adding NMEA0183
2025-07-29 Adding NMEA2000
2025-07-29 Schematics Folder
2025-07-29 Adding UART
2025-07-29 Adding Frontpanel
2025-07-29 Adding Transponder Firmware v11.9.2
2025-07-29 Adding Firmwares
2025-07-29 Updating FW
2025-07-29 Adding CAD
2025-07-29 adding link to CAD
2025-07-29 main readme
2025-07-29 adding assembly manual, v1.0
2025-08-05 update assembly manual
2026-03-22 Add MAIANA AIS firmware build for VS Code and PlatformIO
    Introduce Firmware/Maiana_Blue_AIS_Firmware_VSCode_PlatformIO next to the
    existing STM32CubeIDE project. The tree carries the same application and BSP
    sources, wired for PlatformIO with platformio.ini environments for L4 targets
    (L432/L412), new vs legacy breakouts, and bootloader vector offset where needed.
    - Maintainer README comparing this layout to the CubeIDE sibling
    - Post-build script to copy firmware.bin into Binaries/ with an encoded name
2026-03-22 PlatformIO: version Binaries/ firmware images in git
    Stop ignoring Binaries/*.bin, add current post-build image, and document
    that release binaries under Binaries/ are tracked.
    Made-with: Cursor
2026-03-22 Antenna Parts - v4.2
    Made-with: Cursor
